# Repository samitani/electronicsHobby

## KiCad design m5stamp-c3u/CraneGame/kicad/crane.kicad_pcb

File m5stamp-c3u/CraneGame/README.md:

# What is this ?

CraneGame but it has only 2 axies.

# Parts

| Parts            | Name                 |
|------------------|----------------------|
| Micro Controller | M5Stamp C3U      x 1 |
| Motor Driver     | Toshiba TB6674PG x 2 |
| Bipolar Stepper Motor | MDP-35A     x 1 |
| Bipolar Stepper Motor | [SM-42BYG011](https://akizukidenshi.com/catalog/g/g105372/) x 1 |
| Servo Motor      | [TowerPro MG90S](https://akizukidenshi.com/catalog/g/g113227/)   x 1 |
| Capacitor        | 470uF x 2, 0.1uF x 2 |
| Joystick Module  | [ジョイスティックRKJXV122400R DIP化キット](https://akizukidenshi.com/catalog/g/g115433/) |
| Linear DC/DC Regulator | [ROHM 5V BP5293-50](https://akizukidenshi.com/catalog/g/g111188/) |
| Switch (SW1) | マイクロスイッチ |
| Switch (SW2) | [タクトスイッチ](https://akizukidenshi.com/catalog/g/g103647/) |
# 3D Printings

* [Servo Gripper](https://www.thingiverse.com/thing:3056229)

# Circuit

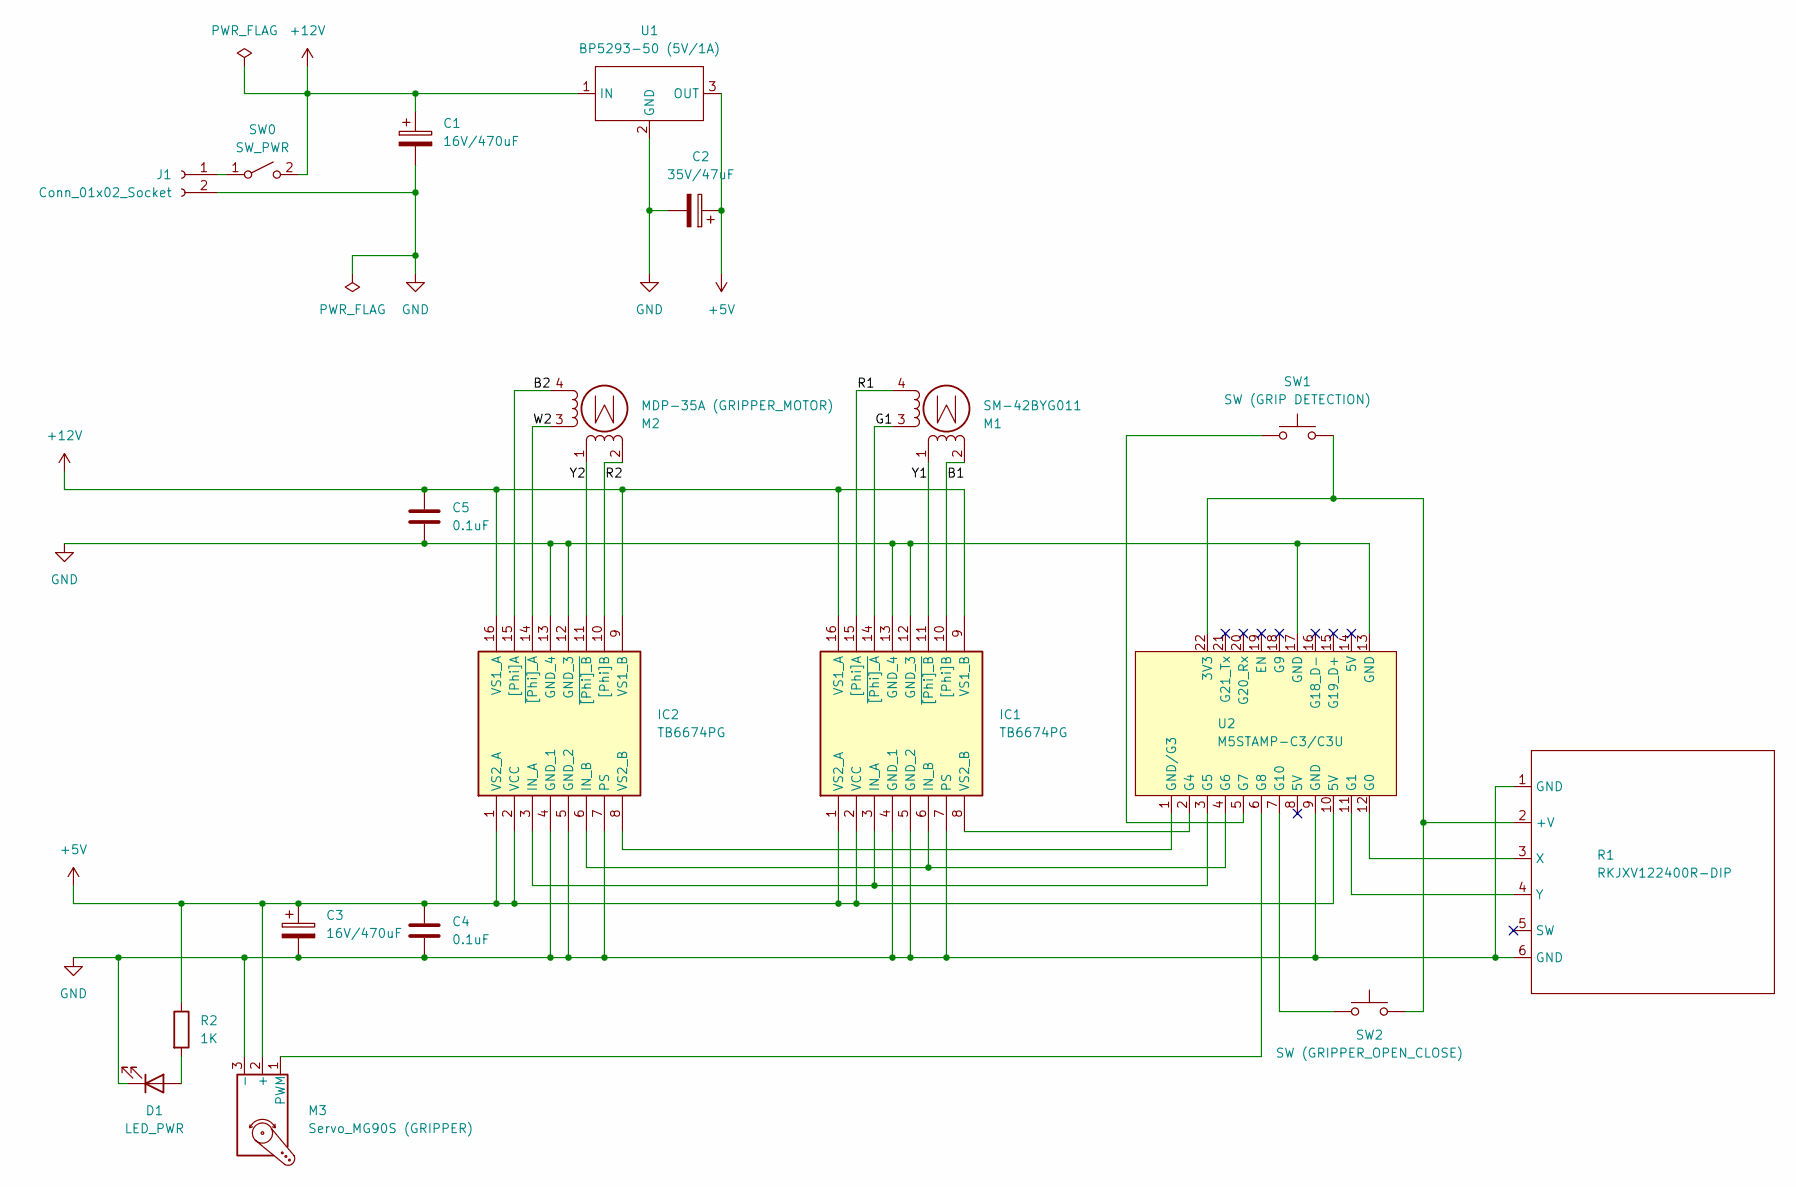
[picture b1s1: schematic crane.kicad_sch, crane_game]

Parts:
C1, C3: 16V/470uF; CP_Radial_D8.0mm_P3.50mm
C2: 35V/47uF; CP_Radial_D5.0mm_P2.00mm
C4, C5: 0.1uF; C_Disc_D5.0mm_W2.5mm_P5.00mm
D1: LED_PWR; LED_D3.0mm
IC1, IC2: TB6674PG; DIP762W60P254L1975H445Q16N; Manufacturer_Part_Number TB6674PG; Mouser Part Number N/A
J1: Conn_01x02_Socket; TerminalBlock_Xinya_XY308-2.54-2P_1x02_P2.54mm_Horizontal
M1: SM-42BYG011; PinHeader_1x04_P2.54mm_Vertical_MOTOR
M2: MDP-35A (GRIPPER_MOTOR); PinHeader_1x04_P2.54mm_Vertical_MOTOR
M3: Servo_MG90S (GRIPPER); PinHeader_1x03_P2.54mm_Vertical
R1: RKJXV122400R-DIP; JOYSTICK
R2: 1K; R_Axial_DIN0309_L9.0mm_D3.2mm_P12.70mm_Horizontal
SW0: SW_PWR; SW_Slide-03_Wuerth-WS-SLTV_10x2.5x6.4_P2.54mm
SW1: SW (GRIP DETECTION); PinHeader_1x02_P2.54mm_Vertical
SW2: SW (GRIPPER_OPEN_CLOSE); SW_PUSH_6mm
U1: BP5293-50 (5V/1A); PinHeader_1x03_P2.54mm_Vertical
U2: M5STAMP-C3/C3U; M5STAMP-C3C3U

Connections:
+5V: C2.1, C3.1, C4.1, IC1.1 (VS2_A), IC1.2 (VCC), IC2.1 (VS2_A), IC2.2 (VCC), M3.2 (+), R2.1, U1.3 (OUT), U2.10 (5V)
+12V: C1.1, C5.1, IC1.9 (VS1_B), IC1.16 (VS1_A), IC2.9 (VS1_B), IC2.16 (VS1_A), SW0.2 (B), U1.1 (IN)
/B1: IC1.10 ([Phi]B), M1.2 (-)
/B2: IC2.15 ([Phi]A), M2.4
/G1: IC1.14 (~[Phi]_A), M1.3
/R1: IC1.15 ([Phi]A), M1.4
/R2: IC2.10 ([Phi]B), M2.2 (-)
/W2: IC2.14 (~[Phi]_A), M2.3
/Y1: IC1.11 (~[Phi]_B), M1.1
/Y2: IC2.11 (~[Phi]_B), M2.1
GND: C1.2, C2.2, C3.2, C4.2, C5.2, D1.1 (K), IC1.4 (GND_1), IC1.5 (GND_2), IC1.7 (PS), IC1.12 (GND_3), IC1.13 (GND_4), IC2.4 (GND_1), IC2.5 (GND_2), IC2.7 (PS), IC2.12 (GND_3), IC2.13 (GND_4), J1.2, M3.3 (-), R1.1 (GND), R1.6 (GND), U1.2 (GND), U2.9 (GND), U2.13 (GND), U2.17 (GND)
unnamed: D1.2 (A), R2.2
unnamed: IC1.3 (IN_A), IC2.3 (IN_A), U2.3 (G5)
unnamed: IC1.6 (IN_B), IC2.6 (IN_B), U2.4 (G6)
unnamed: IC1.8 (VS2_B), U2.2 (G4)
unnamed: IC2.8 (VS2_B), U2.1 (GND/G3)
unnamed: J1.1, SW0.1 (A)
unnamed: M3.1 (PWM), U2.6 (G8)
unnamed: R1.2 (+V), SW1.2, SW2.2, U2.22 (3V3)
unnamed: R1.3 (X), U2.12 (G0)
unnamed: R1.4 (Y), U2.11 (G1)
unnamed: SW1.1, U2.5 (G7)
unnamed: SW2.1, U2.7 (G10)

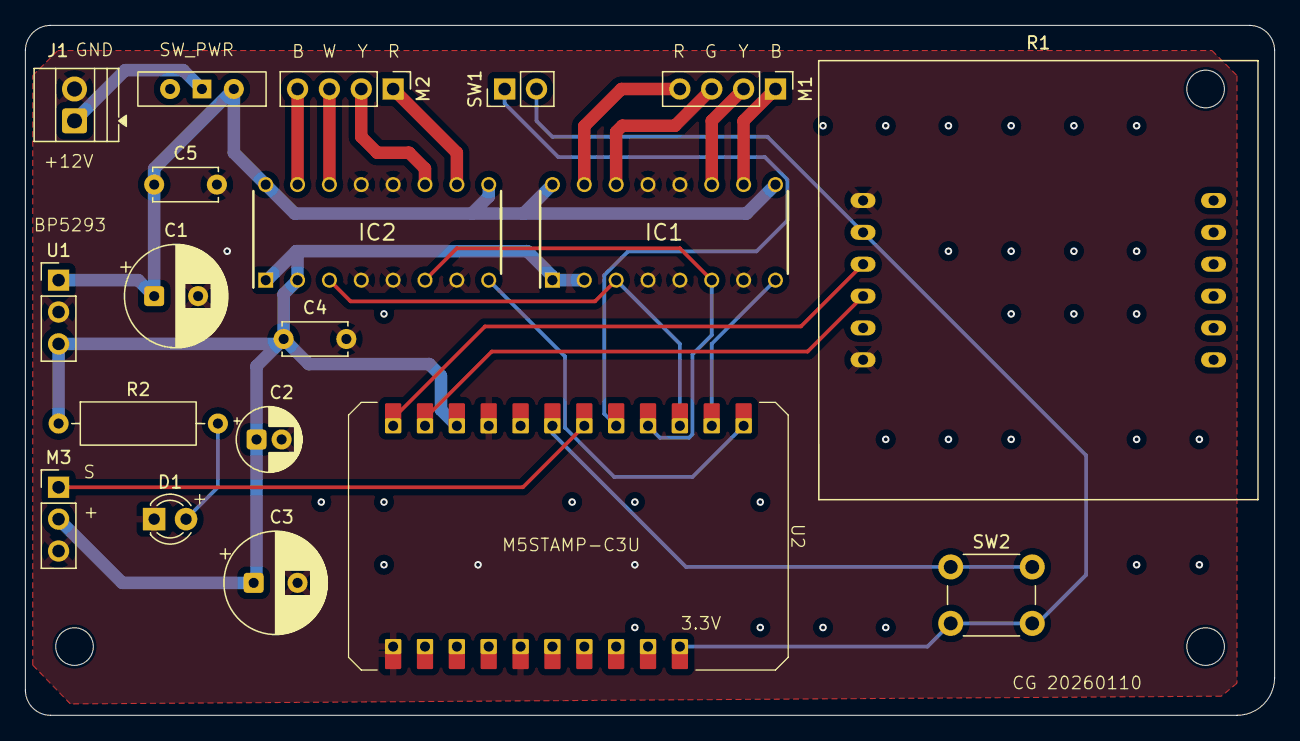
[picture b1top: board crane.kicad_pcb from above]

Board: 2 copper layers, 99.6 x 55.0 mm, 19 parts (0 on the bottom side), 23 nets.

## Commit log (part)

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2025-02-21 added LEDFlux
2025-02-21 rename dir
2025-02-21 added LEDButton
2025-02-22 added Fritzing
2025-03-02 added TB6447PG motordriver sample
2025-03-02 renamed
2025-03-08 added MG996R sample
2025-03-09 added README.md
2025-03-09 draft breadboard
2025-03-09 Update Fritzing file
2025-03-09 added photos
2025-03-09 fixed typo
2025-03-09 Create LICENSE
2025-03-20 added ottoESP32
2025-03-20 moved
2025-03-20 rm LICENSE
2025-09-13 added tempRecorderAHT21B
2025-09-13 fixed dir
2025-12-22 use PlatformIO
2025-12-25 fixed README.md
2025-12-26 rev.2
2025-12-26 added a capacitor
2025-12-30 added lottery function
2026-01-23 PCB version
2026-01-23 added KiCAD files
2026-01-23 Add switch details to README.md
2026-02-03 added MG996R-360-Servo
2026-02-03 fixed animation
2026-02-03 initial version
2026-02-11 [BikkuraPon] initial commit
2026-02-11 added images
2026-05-16 [TinyTermo] added initial program
